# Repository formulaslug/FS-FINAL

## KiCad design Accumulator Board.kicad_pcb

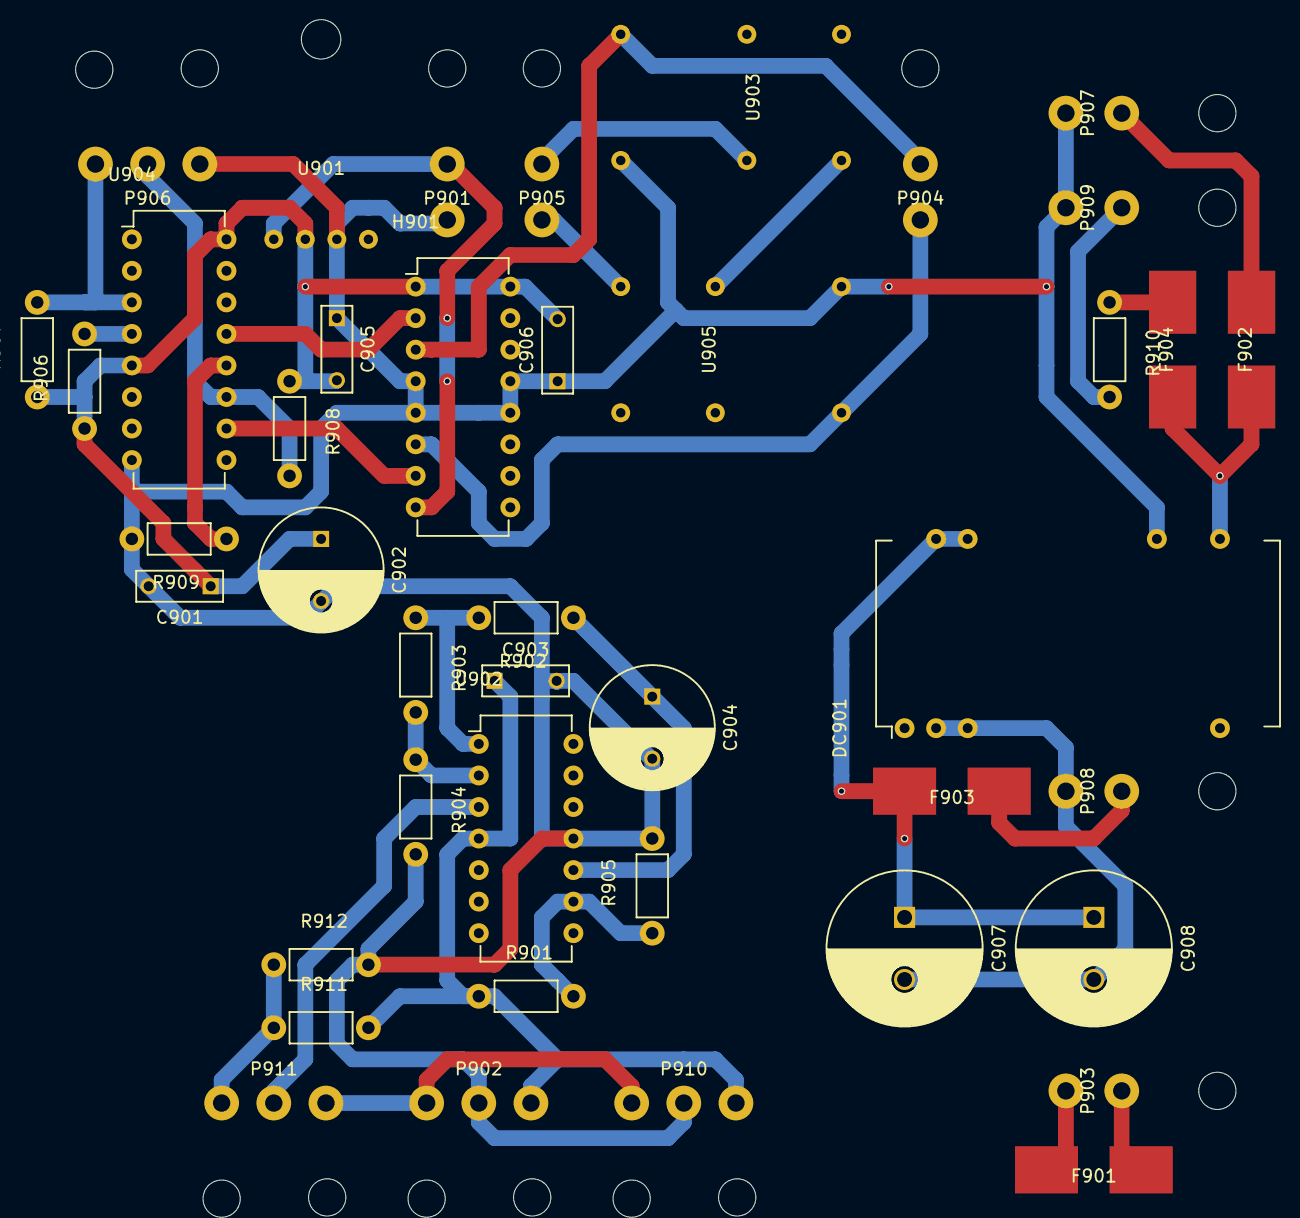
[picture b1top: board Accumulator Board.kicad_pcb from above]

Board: 2 copper layers, 42 parts (0 on the bottom side), 31 nets.

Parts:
C901, C903, C905, C906: .47uF; C_Rect_L7_W2.5_P5
C902: 10uF; C_Radial_D10_L13_P5
C904: .1uF; C_Radial_D10_L13_P5
C907, C908: 100uF; C_Radial_D12.5_L25_P5
DC901: RDD08110S12
F901, F902, F904: 10A; SMD Fuse
F903: DC-DC Fuse; SMD Fuse
H901: SN754410; DIP-16_W7.62mm
P901, P903, P904, P905, P907, P908, P909: CONN_02_B2B; Molex_39-30-0020
P902: CUR_in; Molex_39-30-3036
P906: CONN_03_B2B; Molex_39-30-3036
P910: CUR_out; Molex_39-30-3036
P911: BSPD_Test; Molex_39-30-3036
R901, R905, R906, R907, R908: 10K; Resistor_Horizontal_RM7mm
R902: 8.2K; Resistor_Horizontal_RM7mm
R903: 240; Resistor_Horizontal_RM7mm
R904: 1K; Resistor_Horizontal_RM7mm
R909: 2.2K; Resistor_Horizontal_RM7mm
R910, R911, R912: R; Resistor_Horizontal_RM7mm
U901: PQ05RR12; 4 pin reg
U902: MCP6004; DIP-14_W7.62mm
U903, U905: DK1A1B-12V
U904: CD4044B; DIP-16_W7.62mm

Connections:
/5V: C901.1, C902.1, C905.2, C906.2, H901.1, H901.16, R906.1, R907.1, R908.1, U901.2, U904.5, U904.16
/12V: H901.8, P901.1, U901.1
/ACC_LED+: P909.1, R910.2
/AIRS_IN: P905.1, U903.3
/AIRS_OUT: P905.2, U905.4
/B+_IN: F901.2, P903.1
/B+_OUT: F901.1, P903.2
/BMS_FLT: R906.2, U904.4
/BMS_RES: P906.1, R907.2, U904.3
/BMS_SIG: H901.3, P904.1, U903.8
/CUR_5V: C903.1, P902.1, P910.1, R901.1, R911.2, U902.4
/CUR_SEN: P902.3, P910.3, P911.1
/GND: C901.2, C902.2, C903.2, C904.2, C905.1, C906.1, DC901.16, H901.4, H901.5, H901.12, H901.13, P901.2, P902.2, P906.3, P907.2, P909.2, P910.2, R904.2, R905.2, R909.2, R912.2, U901.3, U902.11, U903.1, U904.8, U905.1
/HV+: F903.2, P908.1
/HV-: C907.2, C908.2, DC901.2, DC901.3, P908.2
/IMD_FLT: R909.1, U904.12
/IMD_RES: P906.2, R908.2, U904.11
/IMD_SIG: H901.6, P904.2, U905.8
/TSAL_12V: F902.1, P907.1
unnamed: C904.1, R902.1, U902.10
unnamed: C907.1, C908.1, DC901.22, DC901.23, F903.1
unnamed: DC901.14, F902.2, F904.2
unnamed: F904.1, R910.1
unnamed: H901.2, U904.13
unnamed: H901.7, U904.10
unnamed: P911.2, U902.3
unnamed: P911.3, R911.1, R912.1
unnamed: R901.2, R905.1, U902.9
unnamed: R902.2, R903.1, U902.1
unnamed: R903.2, R904.1, U902.2
unnamed: U903.4, U905.3

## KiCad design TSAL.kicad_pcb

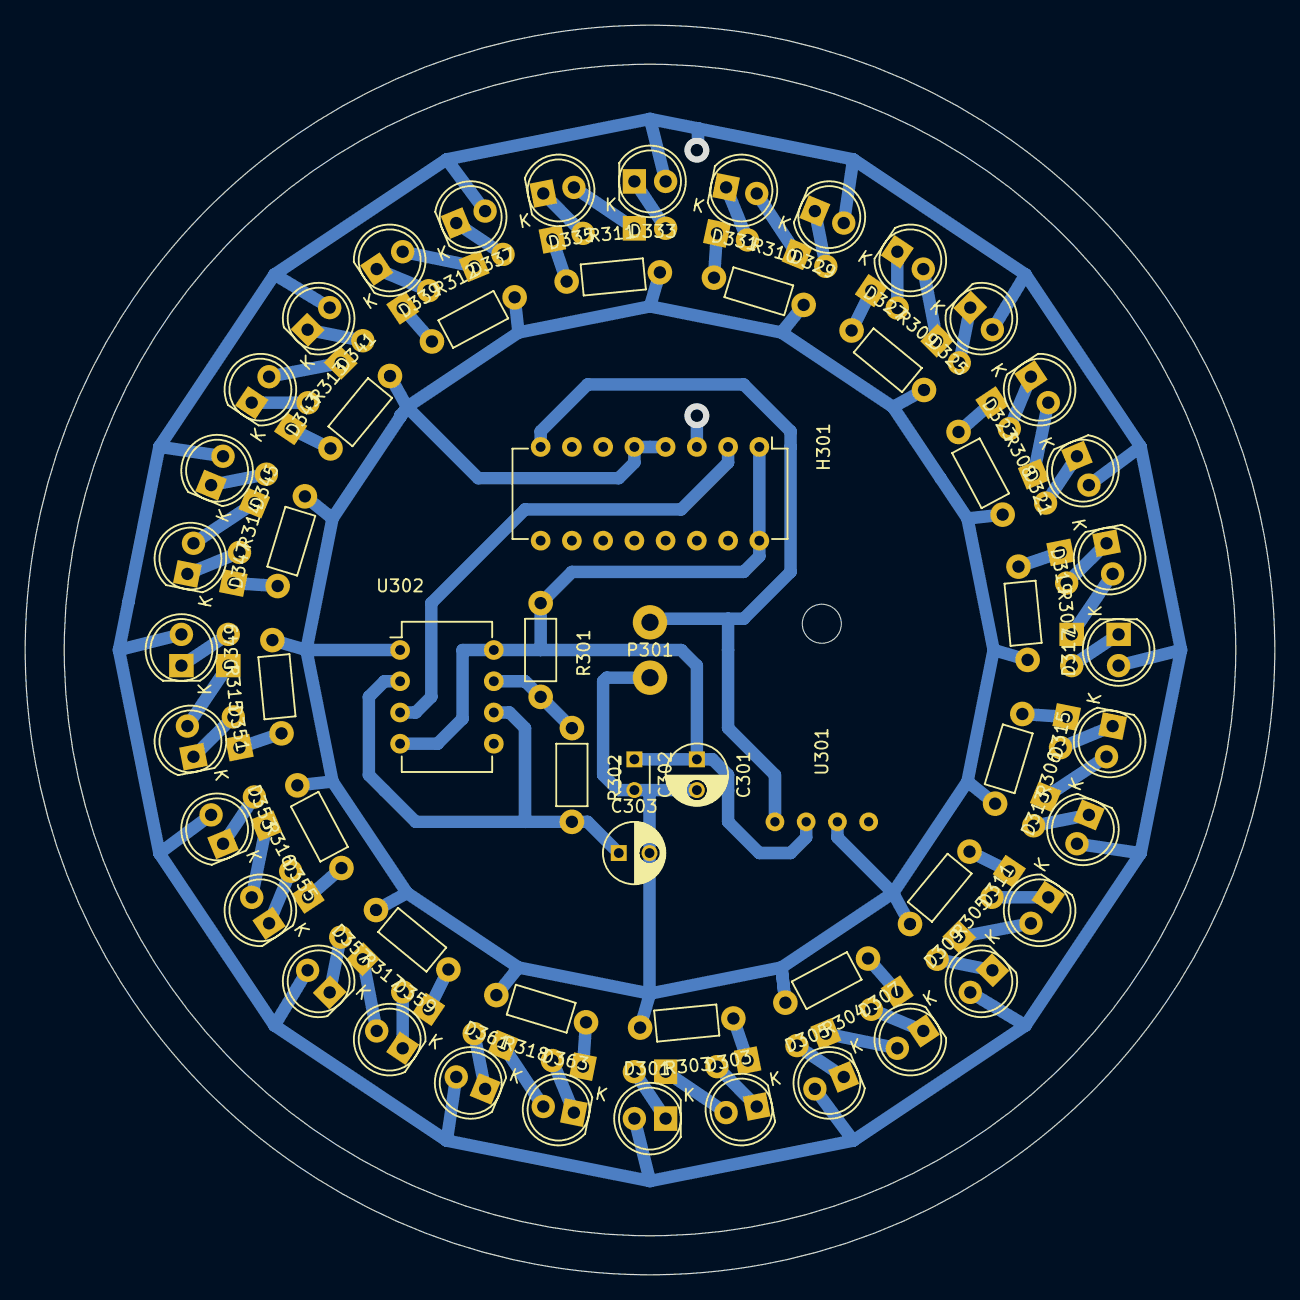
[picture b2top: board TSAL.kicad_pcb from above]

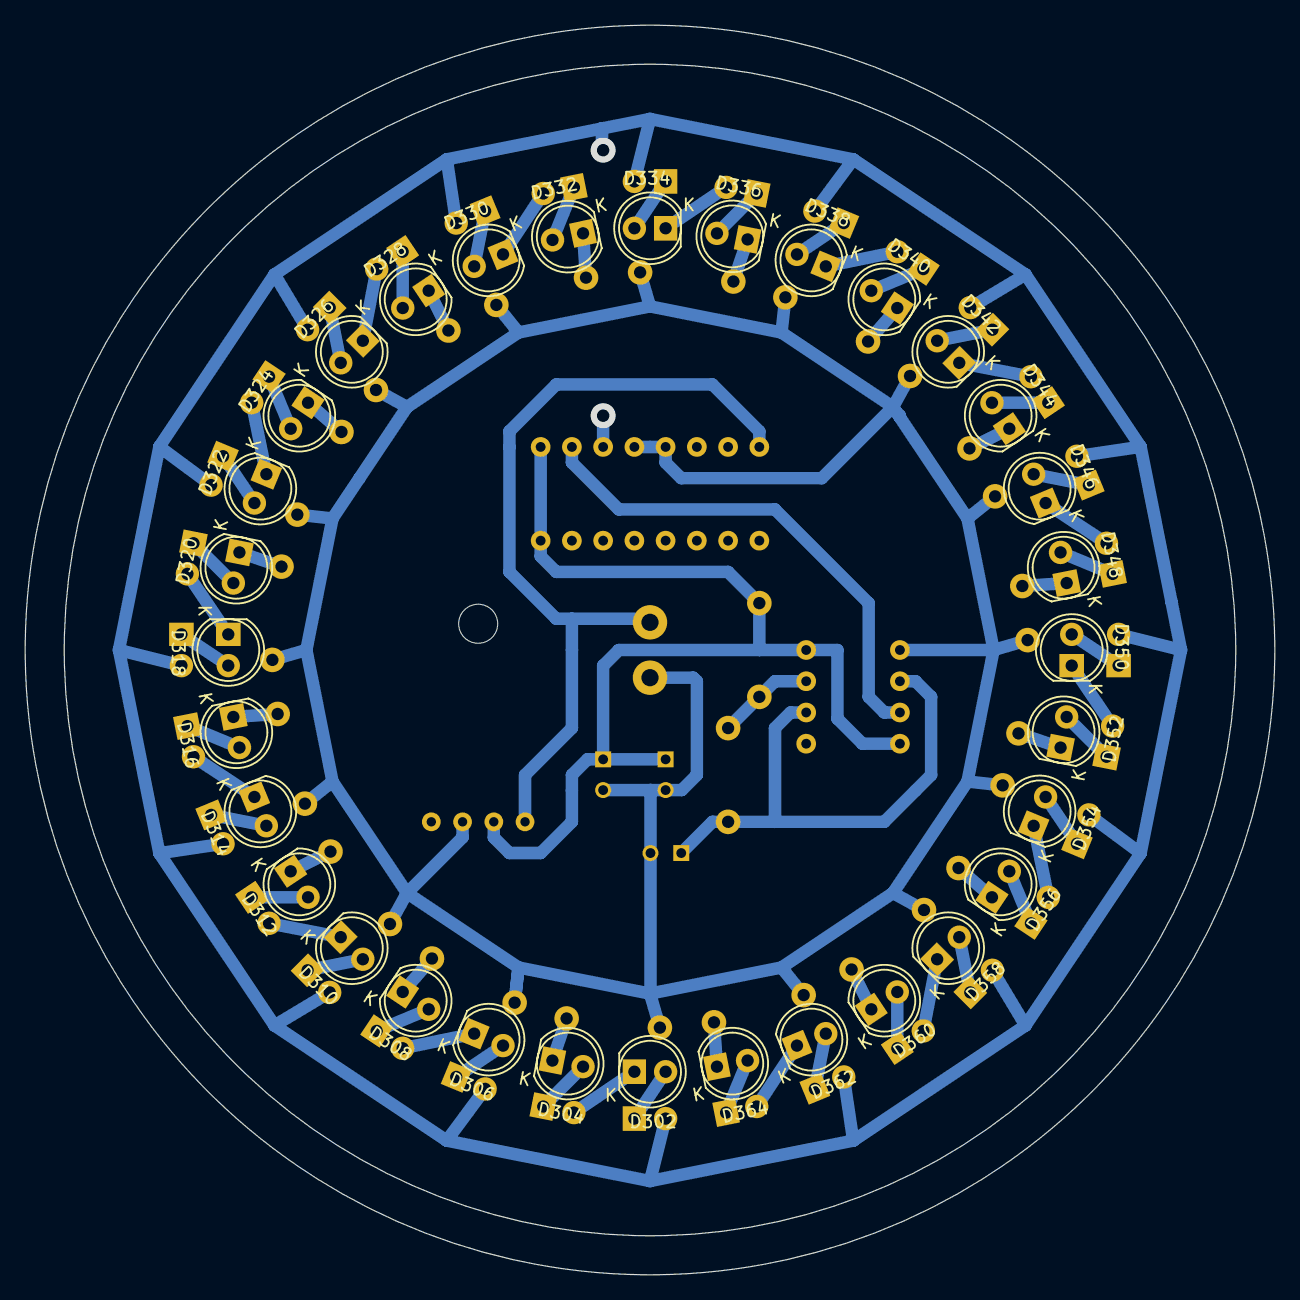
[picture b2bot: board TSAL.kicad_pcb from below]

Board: 2 copper layers, 101.6 x 101.6 mm, 89 parts (32 on the bottom side), 71 nets.

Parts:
C301, C303: 10uF; C_Radial_D5_L6_P2.5
C302: .47uF; C_Disc_D3_P2.5
D301, D302, D303, D304, D305, D306, D307, D308, D309, D310, D311, D312, D313, D314, D315, D316, D317, D318, D319, D320, D321, D322, D323, D324, D325, D326, D327, D328, D329, D330, D331, D332, D333, D334, D335, D336, D337, D338, D339, D340, D341, D342, D343, D344, D345, D346, D347, D348, D349, D350, D351, D352, D353, D354, D355, D356, D357, D358, D359, D360, D361, D362, D363, D364: Led_Small; LED-5MM
H301: SN754410; DIP-16_W7.62mm
P301: CONN_01X02; Molex_39-28-8020
R301, R302: 15K; Resistor_Horizontal_RM7mm
R303, R304, R305, R306, R307, R308, R309, R310, R311, R312, R313, R314, R315, R316, R317, R318: 180; Resistor_Horizontal_RM7mm
U301: PQ05RR12; 4 pin reg
U302: LM555N; DIP-8_W7.62mm

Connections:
/5V: C301.1, C302.1, H301.1, H301.16, R301.1, U301.2, U302.4, U302.8
/12V: H301.8, P301.1, U301.1
/GND: C301.2, C302.2, C303.2, H301.4, H301.5, H301.12, H301.13, P301.2, R303.2, R304.2, R305.2, R306.2, R307.2, R308.2, R309.2, R310.2, R311.2, R312.2, R313.2, R314.2, R315.2, R316.2, R317.2, R318.2, U301.3, U302.1
/OSC: D301.2, D305.2, D309.2, D313.2, D317.2, D321.2, D325.2, D329.2, D333.2, D337.2, D341.2, D345.2, D349.2, D353.2, D357.2, D361.2, H301.3
unnamed: C303.1, R302.2, U302.2, U302.6
unnamed: D301.1, D302.2
unnamed: D302.1, D303.2
unnamed: D303.1, D304.2
unnamed: D304.1, R303.1
unnamed: D305.1, D306.2
unnamed: D306.1, D307.2
unnamed: D307.1, D308.2
unnamed: D308.1, R304.1
unnamed: D309.1, D310.2
unnamed: D310.1, D311.2
unnamed: D311.1, D312.2
unnamed: D312.1, R305.1
unnamed: D313.1, D314.2
unnamed: D314.1, D315.2
unnamed: D315.1, D316.2
unnamed: D316.1, R306.1
unnamed: D317.1, D318.2
unnamed: D318.1, D319.2
unnamed: D319.1, D320.2
unnamed: D320.1, R307.1
unnamed: D321.1, D322.2
unnamed: D322.1, D323.2
unnamed: D323.1, D324.2
unnamed: D324.1, R308.1
unnamed: D325.1, D326.2
unnamed: D326.1, D327.2
unnamed: D327.1, D328.2
unnamed: D328.1, R309.1
unnamed: D329.1, D330.2
unnamed: D330.1, D331.2
unnamed: D331.1, D332.2
unnamed: D332.1, R310.1
unnamed: D333.1, D334.2
unnamed: D334.1, D335.2
unnamed: D335.1, D336.2
unnamed: D336.1, R311.1
unnamed: D337.1, D338.2
unnamed: D338.1, D339.2
unnamed: D339.1, D340.2
unnamed: D340.1, R312.1
unnamed: D341.1, D342.2
unnamed: D342.1, D343.2
unnamed: D343.1, D344.2
unnamed: D344.1, R313.1
unnamed: D345.1, D346.2
unnamed: D346.1, D347.2
unnamed: D347.1, D348.2
unnamed: D348.1, R314.1
unnamed: D349.1, D350.2
unnamed: D350.1, D351.2
unnamed: D351.1, D352.2
unnamed: D352.1, R315.1
unnamed: D353.1, D354.2
unnamed: D354.1, D355.2
unnamed: D355.1, D356.2
unnamed: D356.1, R316.1
unnamed: D357.1, D358.2
unnamed: D358.1, D359.2
unnamed: D359.1, D360.2
unnamed: D360.1, R317.1
unnamed: D361.1, D362.2
unnamed: D362.1, D363.2
unnamed: D363.1, D364.2
unnamed: D364.1, R318.1
unnamed: H301.2, U302.3
unnamed: R301.2, R302.1, U302.7

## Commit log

2016-04-25 Added files via upload
